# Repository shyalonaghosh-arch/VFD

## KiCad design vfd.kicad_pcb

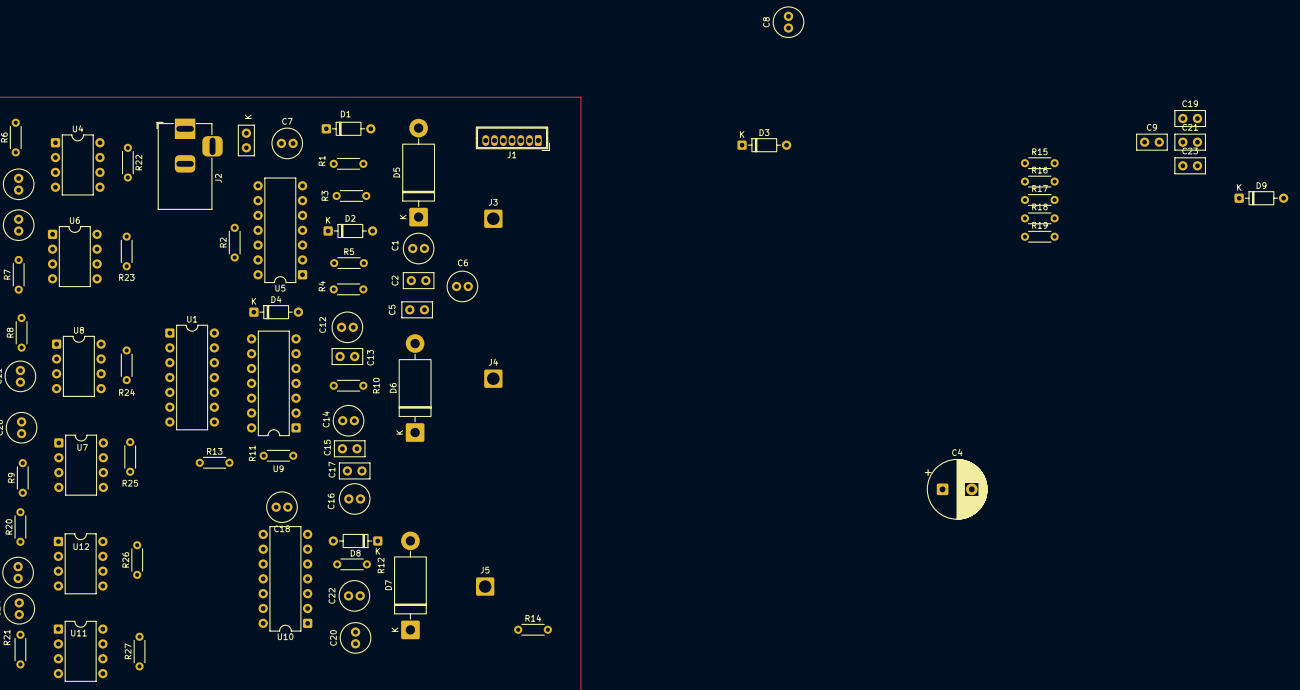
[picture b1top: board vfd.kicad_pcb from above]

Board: 2 copper layers, 78 parts (0 on the bottom side), 50 nets.

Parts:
C1, C16, C22: 2.2uF; C_Radial_D5.0mm_H11.0mm_P2.00mm
C2, C5, C10, C13, C15, C17, C19, C21, C23: 100nF; C_Disc_D5.0mm_W2.5mm_P2.50mm
C3, C6, C11, C14, C20, C24, C25, C26, C27: 10uF; C_Radial_D5.0mm_H11.0mm_P2.00mm
C4: 680uF / 50v; CP_Radial_D10.0mm_P5.00mm
C7, C12, C18: 1uF; C_Radial_D5.0mm_H11.0mm_P2.00mm
C8: 1uF / 50v; C_Radial_D5.0mm_H11.0mm_P2.00mm
C9: 100nF / 50 v; C_Disc_D5.0mm_W2.5mm_P2.50mm
D1, D2, D3, D4, D8, D9: 1N4148; D_DO-35_SOD27_P7.62mm_Horizontal
D5, D6, D7: UF5403; D_DO-201AD_P15.24mm_Horizontal
J1: Conn_01x07_Pin; Wuerth_WR-WTB_64800711622_1x07_P1.50mm_Vertical
J2: Conn_01x02_Pin; BarrelJack_Horizontal
J3, J4, J5: Conn_01x01_Pin; SolderWire-1.5sqmm_1x01_D1.7mm_OD3mm
R1, R5, R11, R12, R16, R17: 10; R_Axial_DIN0204_L3.6mm_D1.6mm_P5.08mm_Horizontal
R2, R10, R15: 10k; R_Axial_DIN0204_L3.6mm_D1.6mm_P5.08mm_Horizontal
R3, R4, R13, R14, R18, R19: 4.7k; R_Axial_DIN0204_L3.6mm_D1.6mm_P5.08mm_Horizontal
R6, R7, R8, R9, R20, R21: 390; R_Axial_DIN0204_L3.6mm_D1.6mm_P5.08mm_Horizontal
R22, R23, R24, R25, R26, R27: 1k; R_Axial_DIN0204_L3.6mm_D1.6mm_P5.08mm_Horizontal
U1: 74hc14-dip-ic; DIP-14_W7.62mm
U4, U6, U7, U8, U11, U12: 6N137; DIP-8_W7.62mm
U5, U9, U10: IR2112; DIP-14_W7.62mm

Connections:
+5V: C3.1, C7.1, C10.1, C11.1, C12.1, C13.1, C18.1, C19.1, C24.1, C25.2, C26.2, C27.2, R22.1, R23.1, R24.1, R25.1, R26.1, R27.1, U1.14 (VCC), U4.7 (EN), U4.8 (VCC), U5.9 (VDD), U6.7 (EN), U6.8 (VCC), U7.7 (EN), U7.8 (VCC), U8.7 (EN), U8.8 (VCC), U9.9 (VDD), U10.9 (VDD), U11.7 (EN), U11.8 (VCC), U12.7 (EN), U12.8 (VCC)
+12V: C5.1, C6.1, C14.1, C15.1, C20.1, C21.1, D5.2 (A), D6.2 (A), D7.2 (A), U5.3 (VCC), U9.3 (VCC), U10.3 (VCC)
+24V: C4.1, C8.1, C9.1, J2.1
/PWM_AH: J1.5, R6.1
/PWM_AL: J1.6, R7.1
/PWM_BH: J1.4, R8.1
/PWM_BL: J1.3, R9.1
/PWM_CH: J1.2, R20.1
/PWM_CL: J1.1, R21.1
/nano-GND: J1.7, U4.3 (C), U6.3 (C), U7.3 (C), U8.3 (C), U11.3 (C), U12.3 (C)
/phase A: C1.1, C2.2, J3.1 (Pin_1_1), R3.1, U5.5 (VS)
/phase B: C16.1, C17.2, J4.1 (Pin_1_1), R14.1, U9.5 (VS)
/phase C: C22.1, C23.2, J5.1 (Pin_1_1), R19.1, U10.5 (VS)
GND: C3.2, C4.2, C5.2, C6.2, C7.2, C8.2, C9.2, C10.2, C11.2, C12.2, C13.2, C14.2, C15.2, C18.2, C19.2, C20.2, C21.2, C24.2, C25.1, C26.1, C27.1, J2.2, R2.1, R4.1, R10.1, R13.1, R15.1, R18.1, U1.7 (GND), U4.5 (GND), U5.2 (COM), U5.13 (VSS), U6.5 (GND), U7.5 (GND), U8.5 (GND), U9.2 (COM), U9.13 (VSS), U10.2 (COM), U10.13 (VSS), U11.5 (GND), U12.5 (GND)
unnamed: D1.2 (A), R1.2, R3.2
unnamed: D1.1 (K), R1.1, U5.7 (HO)
unnamed: D2.2 (A), R4.2, R5.2
unnamed: D2.1 (K), R5.1, U5.1 (LO)
unnamed: D3.2 (A), R11.2, R13.2
unnamed: D3.1 (K), R11.1, U9.1 (LO)
unnamed: D4.2 (A), R12.2, R14.2
unnamed: D4.1 (K), R12.1, U9.7 (HO)
unnamed: C1.2, C2.1, D5.1 (K), U5.6 (VB)
unnamed: C16.2, C17.1, D6.1 (K), U9.6 (VB)
unnamed: C22.2, C23.1, D7.1 (K), U10.6 (VB)
unnamed: D8.2 (A), R16.2, R18.2
unnamed: D8.1 (K), R16.1, U10.1 (LO)
unnamed: D9.2 (A), R17.2, R19.2
unnamed: D9.1 (K), R17.1, U10.7 (HO)
unnamed: R22.2, U1.1 (A1), U4.6 (VO)
unnamed: R24.2, U1.3 (A2), U7.6 (VO)
unnamed: R26.2, U1.5 (A3), U11.6 (VO)
unnamed: R27.2, U1.9 (A4), U12.6 (VO)
unnamed: R25.2, U1.11 (A5), U8.6 (VO)
unnamed: R23.2, U1.13 (A6), U6.6 (VO)
unnamed: U1.2 (Y1), U5.10 (HIN)
unnamed: U1.4 (Y2), U9.10 (HIN)
unnamed: U1.6 (Y3), U10.10 (HIN)
unnamed: U1.8 (Y4), U10.12 (LIN)
unnamed: U1.10 (Y5), U9.12 (LIN)
unnamed: U1.12 (Y6), U5.12 (LIN)
unnamed: R6.2, U4.2 (A)
unnamed: R2.2, U5.11 (SD)
unnamed: R7.2, U6.2 (A)
unnamed: R8.2, U7.2 (A)
unnamed: R9.2, U8.2 (A)
unnamed: R10.2, U9.11 (SD)
unnamed: R15.2, U10.11 (SD)
unnamed: R20.2, U11.2 (A)
unnamed: R21.2, U12.2 (A)
